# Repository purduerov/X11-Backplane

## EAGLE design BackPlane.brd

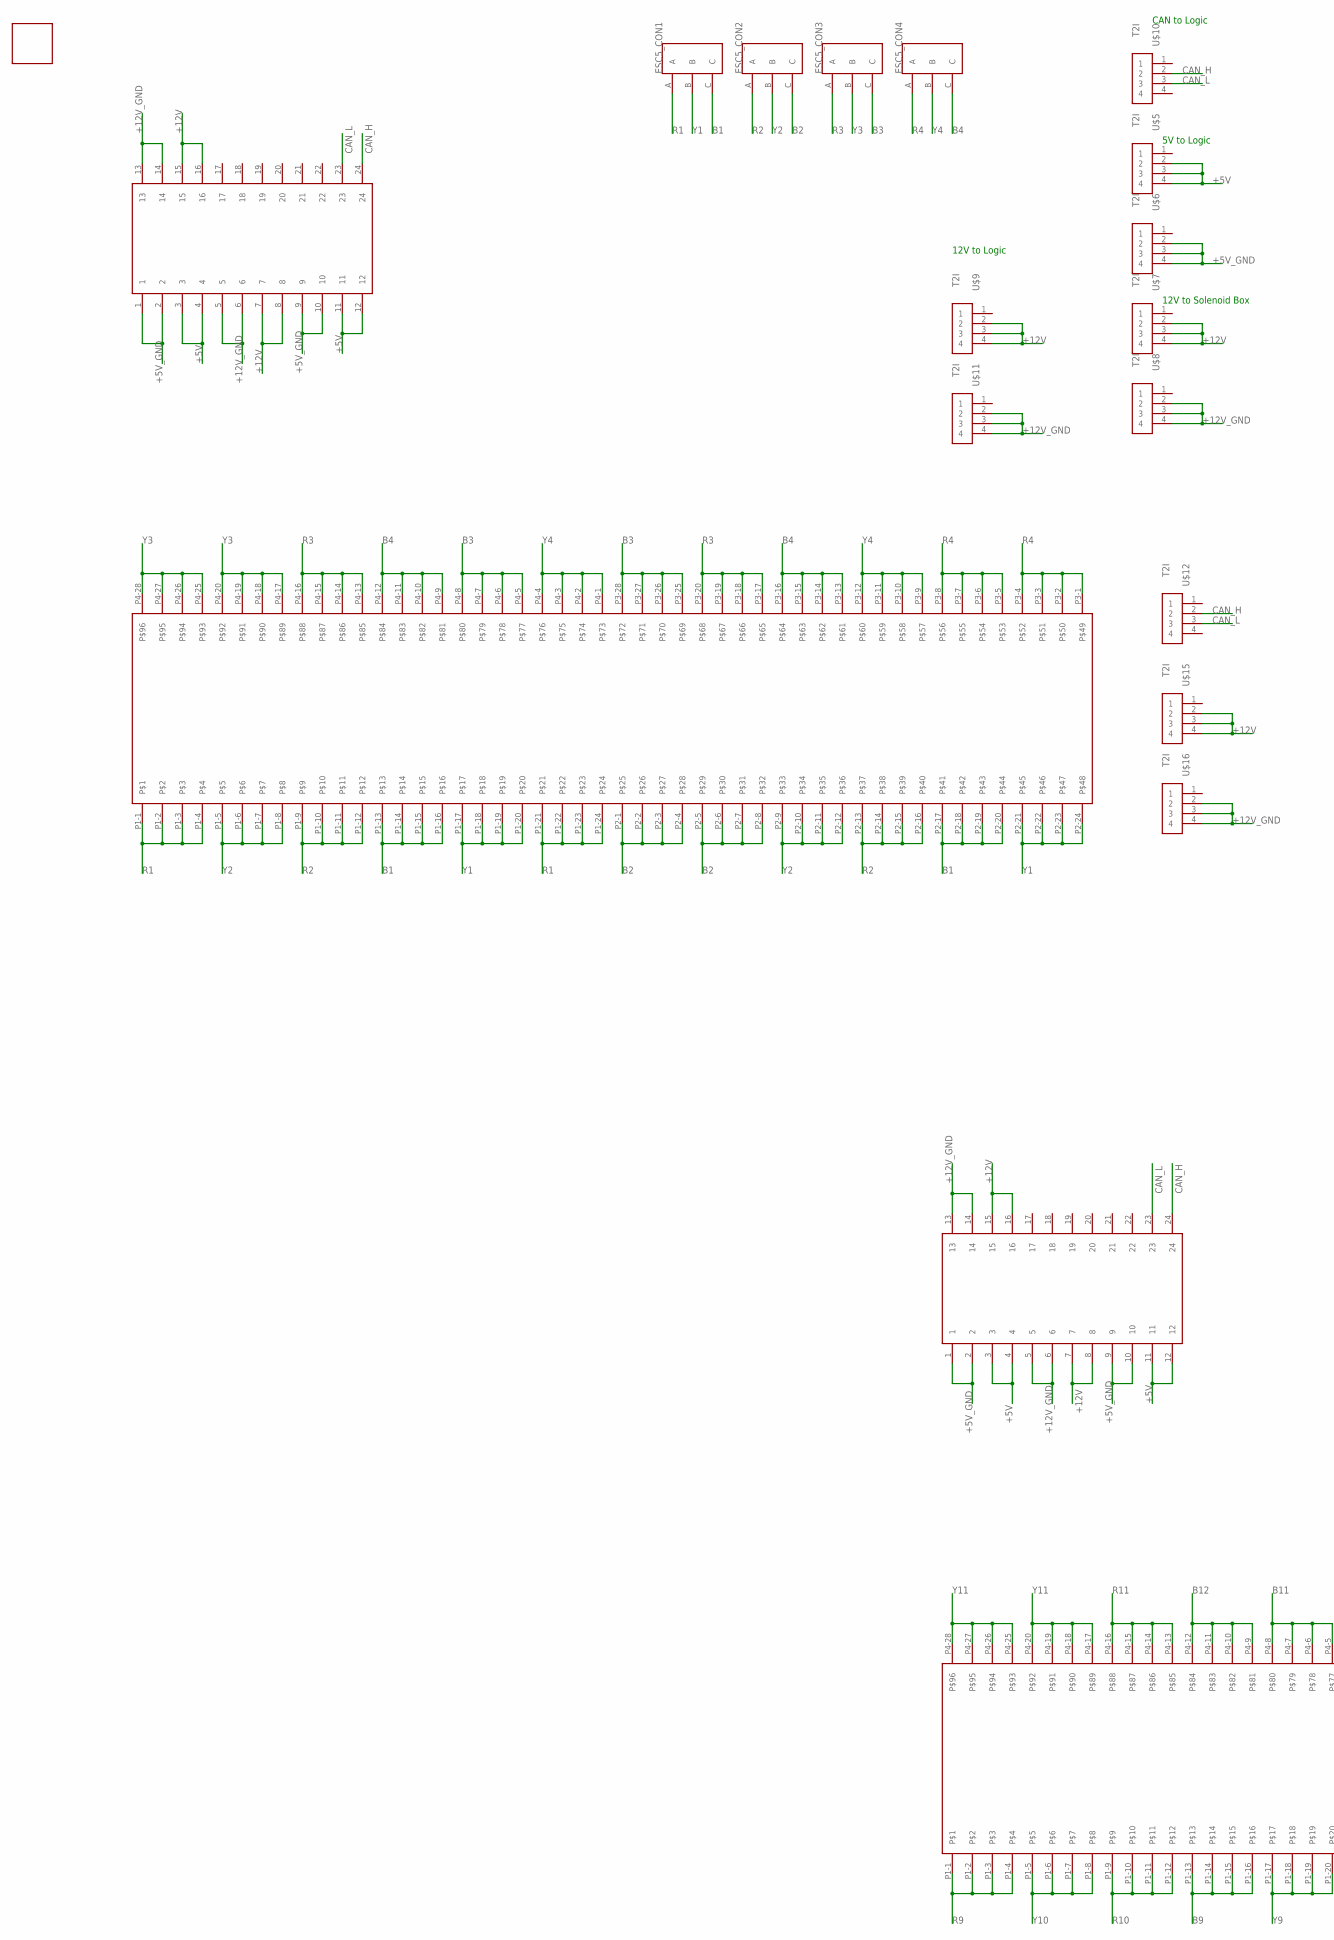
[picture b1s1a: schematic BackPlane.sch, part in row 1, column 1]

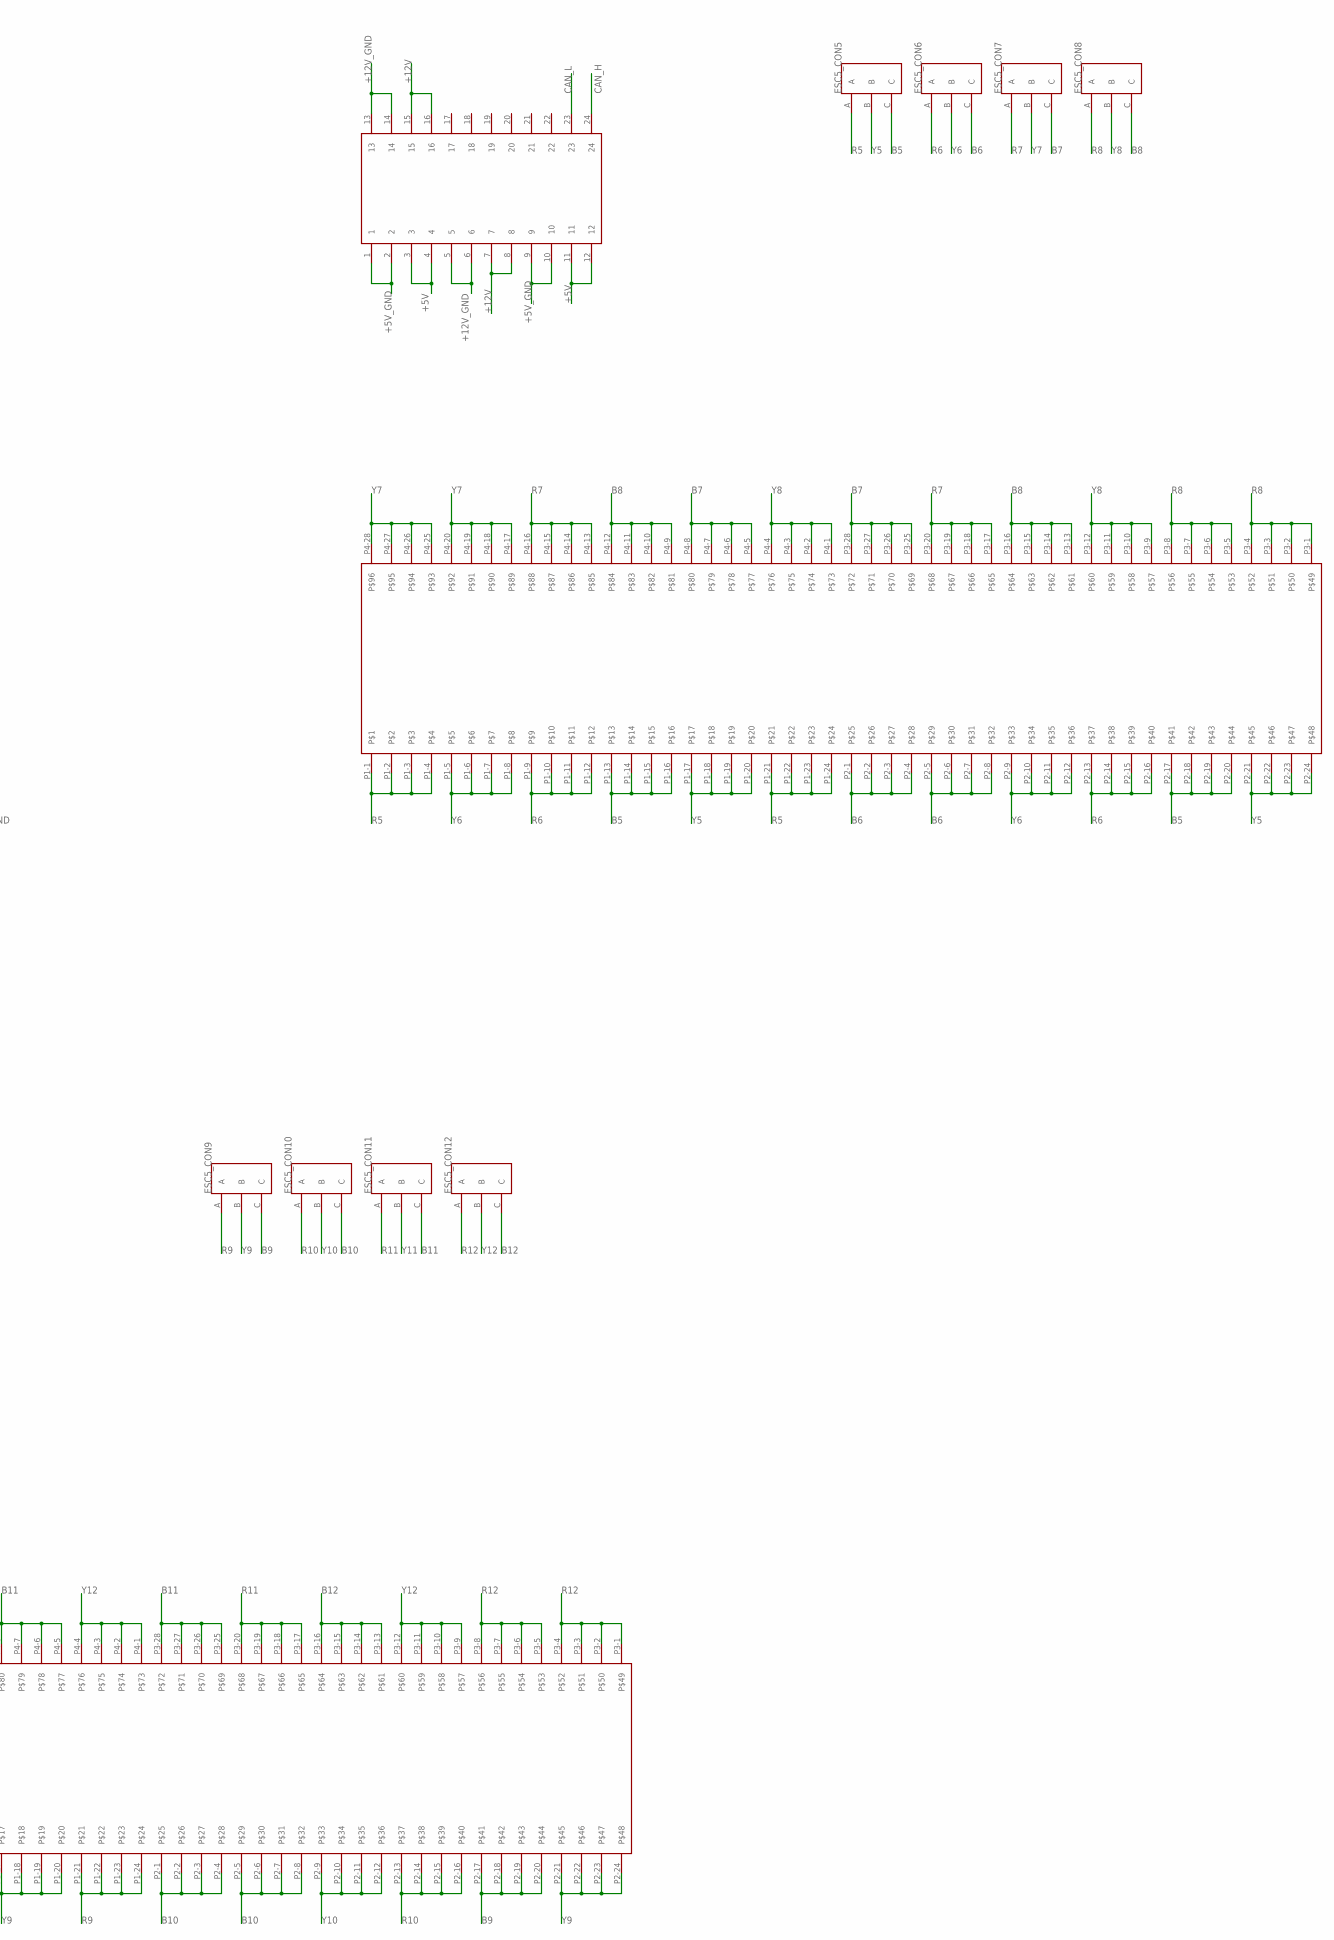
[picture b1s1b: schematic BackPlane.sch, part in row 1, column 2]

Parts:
ESC5_CON1, ESC5_CON2, ESC5_CON3, ESC5_CON4, ESC5_CON5, ESC5_CON6, ESC5_CON7, ESC5_CON8, ESC5_CON9, ESC5_CON10, ESC5_CON11, ESC5_CON12: 3PINCONNECTOR
U$1: BOARDBKP; BKP
U$2, U$3, U$4: THICC_CONNECTOR
U$5, U$6, U$7, U$8, U$9, U$10, U$11, U$12, U$15, U$16: T2I

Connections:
+5V: U$2.3, U$2.4, U$2.11, U$2.12, U$3.3, U$3.4, U$3.11, U$3.12, U$4.3, U$4.4, U$4.11, U$4.12, U$5.2, U$5.3, U$5.4
+5V_GND: U$2.1, U$2.2, U$2.9, U$2.10, U$3.1, U$3.2, U$3.9, U$3.10, U$4.1, U$4.2, U$4.9, U$4.10, U$6.2, U$6.3, U$6.4
+12V: U$2.7, U$2.8, U$2.15, U$2.16, U$3.7, U$3.8, U$3.15, U$3.16, U$4.7, U$4.8, U$4.15, U$4.16, U$7.2, U$7.3, U$7.4, U$9.2, U$9.3, U$9.4, U$15.2, U$15.3, U$15.4
+12V_GND: U$2.5, U$2.6, U$2.13, U$2.14, U$3.5, U$3.6, U$3.13, U$3.14, U$4.5, U$4.6, U$4.13, U$4.14, U$8.2, U$8.3, U$8.4, U$11.2, U$11.3, U$11.4, U$16.2, U$16.3, U$16.4
B1: ESC5_CON1.C, U$2.P1-13, U$2.P1-14, U$2.P1-15, U$2.P1-16, U$2.P2-17, U$2.P2-18, U$2.P2-19, U$2.P2-20
B2: ESC5_CON2.C, U$2.P2-1, U$2.P2-2, U$2.P2-3, U$2.P2-4, U$2.P2-5, U$2.P2-6, U$2.P2-7, U$2.P2-8
B3: ESC5_CON3.C, U$2.P3-25, U$2.P3-26, U$2.P3-27, U$2.P3-28, U$2.P4-5, U$2.P4-6, U$2.P4-7, U$2.P4-8
B4: ESC5_CON4.C, U$2.P3-13, U$2.P3-14, U$2.P3-15, U$2.P3-16, U$2.P4-9, U$2.P4-10, U$2.P4-11, U$2.P4-12
B5: ESC5_CON5.C, U$3.P1-13, U$3.P1-14, U$3.P1-15, U$3.P1-16, U$3.P2-17, U$3.P2-18, U$3.P2-19, U$3.P2-20
B6: ESC5_CON6.C, U$3.P2-1, U$3.P2-2, U$3.P2-3, U$3.P2-4, U$3.P2-5, U$3.P2-6, U$3.P2-7, U$3.P2-8
B7: ESC5_CON7.C, U$3.P3-25, U$3.P3-26, U$3.P3-27, U$3.P3-28, U$3.P4-5, U$3.P4-6, U$3.P4-7, U$3.P4-8
B8: ESC5_CON8.C, U$3.P3-13, U$3.P3-14, U$3.P3-15, U$3.P3-16, U$3.P4-9, U$3.P4-10, U$3.P4-11, U$3.P4-12
B9: ESC5_CON9.C, U$4.P1-13, U$4.P1-14, U$4.P1-15, U$4.P1-16, U$4.P2-17, U$4.P2-18, U$4.P2-19, U$4.P2-20
B10: ESC5_CON10.C, U$4.P2-1, U$4.P2-2, U$4.P2-3, U$4.P2-4, U$4.P2-5, U$4.P2-6, U$4.P2-7, U$4.P2-8
B11: ESC5_CON11.C, U$4.P3-25, U$4.P3-26, U$4.P3-27, U$4.P3-28, U$4.P4-5, U$4.P4-6, U$4.P4-7, U$4.P4-8
B12: ESC5_CON12.C, U$4.P3-13, U$4.P3-14, U$4.P3-15, U$4.P3-16, U$4.P4-9, U$4.P4-10, U$4.P4-11, U$4.P4-12
CAN_H: U$2.24, U$3.24, U$4.24, U$10.2, U$12.2
CAN_L: U$2.23, U$3.23, U$4.23, U$10.3, U$12.3
R1: ESC5_CON1.A, U$2.P1-1, U$2.P1-2, U$2.P1-3, U$2.P1-4, U$2.P1-21, U$2.P1-22, U$2.P1-23, U$2.P1-24
R2: ESC5_CON2.A, U$2.P1-9, U$2.P1-10, U$2.P1-11, U$2.P1-12, U$2.P2-13, U$2.P2-14, U$2.P2-15, U$2.P2-16
R3: ESC5_CON3.A, U$2.P3-17, U$2.P3-18, U$2.P3-19, U$2.P3-20, U$2.P4-13, U$2.P4-14, U$2.P4-15, U$2.P4-16
R4: ESC5_CON4.A, U$2.P3-1, U$2.P3-2, U$2.P3-3, U$2.P3-4, U$2.P3-5, U$2.P3-6, U$2.P3-7, U$2.P3-8
R5: ESC5_CON5.A, U$3.P1-1, U$3.P1-2, U$3.P1-3, U$3.P1-4, U$3.P1-21, U$3.P1-22, U$3.P1-23, U$3.P1-24
R6: ESC5_CON6.A, U$3.P1-9, U$3.P1-10, U$3.P1-11, U$3.P1-12, U$3.P2-13, U$3.P2-14, U$3.P2-15, U$3.P2-16
R7: ESC5_CON7.A, U$3.P3-17, U$3.P3-18, U$3.P3-19, U$3.P3-20, U$3.P4-13, U$3.P4-14, U$3.P4-15, U$3.P4-16
R8: ESC5_CON8.A, U$3.P3-1, U$3.P3-2, U$3.P3-3, U$3.P3-4, U$3.P3-5, U$3.P3-6, U$3.P3-7, U$3.P3-8
R9: ESC5_CON9.A, U$4.P1-1, U$4.P1-2, U$4.P1-3, U$4.P1-4, U$4.P1-21, U$4.P1-22, U$4.P1-23, U$4.P1-24
R10: ESC5_CON10.A, U$4.P1-9, U$4.P1-10, U$4.P1-11, U$4.P1-12, U$4.P2-13, U$4.P2-14, U$4.P2-15, U$4.P2-16
R11: ESC5_CON11.A, U$4.P3-17, U$4.P3-18, U$4.P3-19, U$4.P3-20, U$4.P4-13, U$4.P4-14, U$4.P4-15, U$4.P4-16
R12: ESC5_CON12.A, U$4.P3-1, U$4.P3-2, U$4.P3-3, U$4.P3-4, U$4.P3-5, U$4.P3-6, U$4.P3-7, U$4.P3-8
Y1: ESC5_CON1.B, U$2.P1-17, U$2.P1-18, U$2.P1-19, U$2.P1-20, U$2.P2-21, U$2.P2-22, U$2.P2-23, U$2.P2-24
Y2: ESC5_CON2.B, U$2.P1-5, U$2.P1-6, U$2.P1-7, U$2.P1-8, U$2.P2-9, U$2.P2-10, U$2.P2-11, U$2.P2-12
Y3: ESC5_CON3.B, U$2.P4-17, U$2.P4-18, U$2.P4-19, U$2.P4-20, U$2.P4-25, U$2.P4-26, U$2.P4-27, U$2.P4-28
Y4: ESC5_CON4.B, U$2.P3-9, U$2.P3-10, U$2.P3-11, U$2.P3-12, U$2.P4-1, U$2.P4-2, U$2.P4-3, U$2.P4-4
Y5: ESC5_CON5.B, U$3.P1-17, U$3.P1-18, U$3.P1-19, U$3.P1-20, U$3.P2-21, U$3.P2-22, U$3.P2-23, U$3.P2-24
Y6: ESC5_CON6.B, U$3.P1-5, U$3.P1-6, U$3.P1-7, U$3.P1-8, U$3.P2-9, U$3.P2-10, U$3.P2-11, U$3.P2-12
Y7: ESC5_CON7.B, U$3.P4-17, U$3.P4-18, U$3.P4-19, U$3.P4-20, U$3.P4-25, U$3.P4-26, U$3.P4-27, U$3.P4-28
Y8: ESC5_CON8.B, U$3.P3-9, U$3.P3-10, U$3.P3-11, U$3.P3-12, U$3.P4-1, U$3.P4-2, U$3.P4-3, U$3.P4-4
Y9: ESC5_CON9.B, U$4.P1-17, U$4.P1-18, U$4.P1-19, U$4.P1-20, U$4.P2-21, U$4.P2-22, U$4.P2-23, U$4.P2-24
Y10: ESC5_CON10.B, U$4.P1-5, U$4.P1-6, U$4.P1-7, U$4.P1-8, U$4.P2-9, U$4.P2-10, U$4.P2-11, U$4.P2-12
Y11: ESC5_CON11.B, U$4.P4-17, U$4.P4-18, U$4.P4-19, U$4.P4-20, U$4.P4-25, U$4.P4-26, U$4.P4-27, U$4.P4-28
Y12: ESC5_CON12.B, U$4.P3-9, U$4.P3-10, U$4.P3-11, U$4.P3-12, U$4.P4-1, U$4.P4-2, U$4.P4-3, U$4.P4-4

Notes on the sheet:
12V to Logic
12V to Solenoid Box
5V to Logic
CAN to Logic

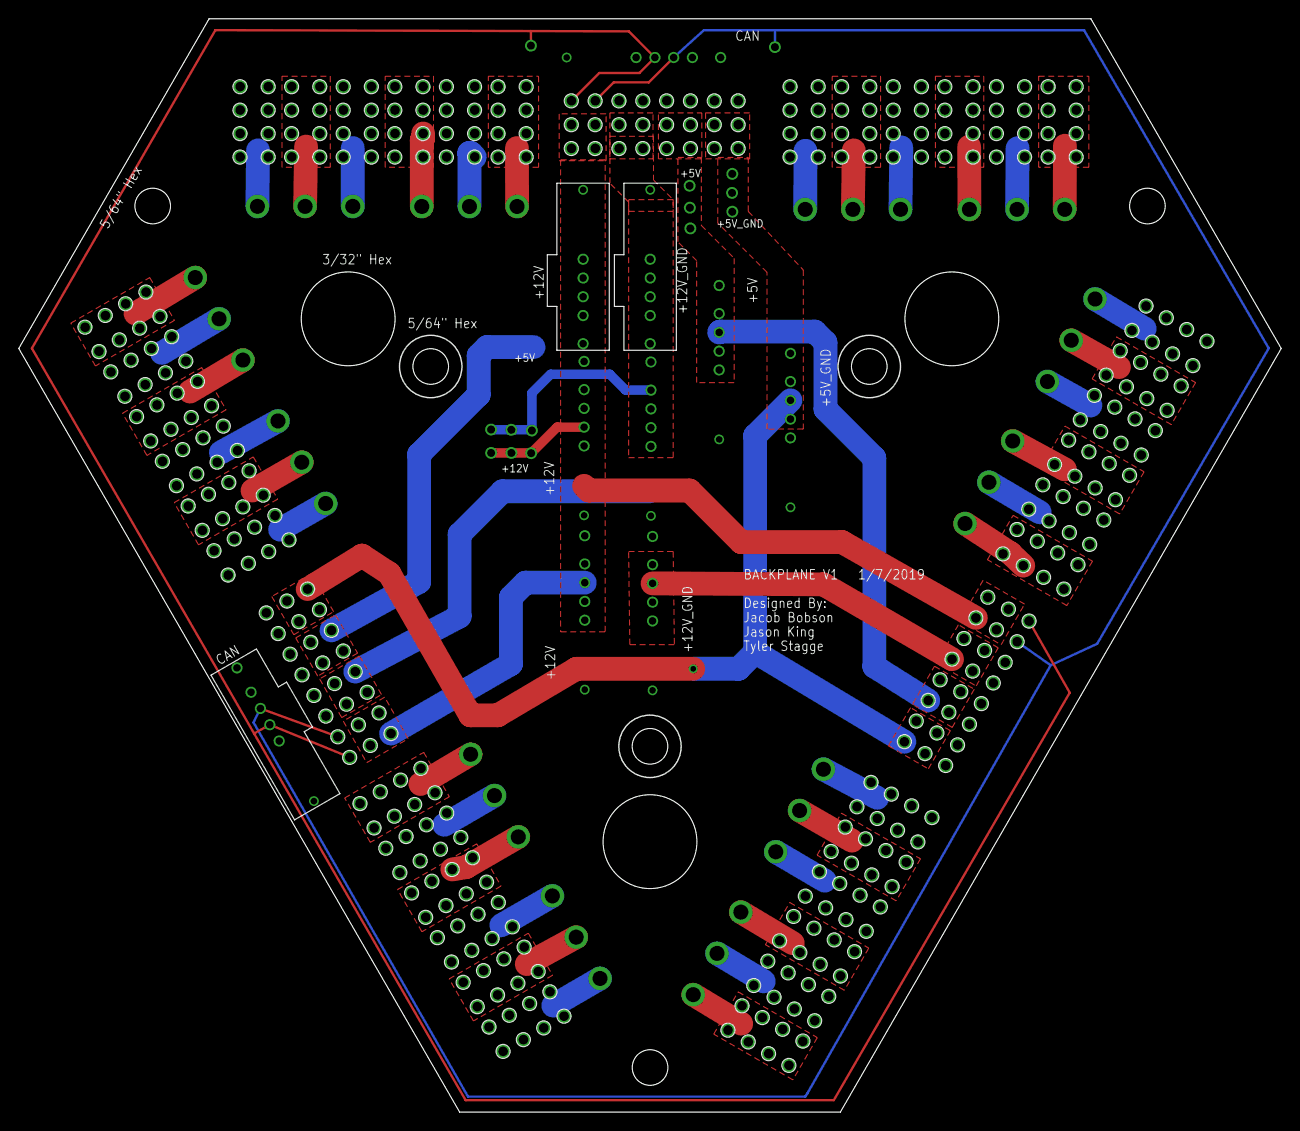
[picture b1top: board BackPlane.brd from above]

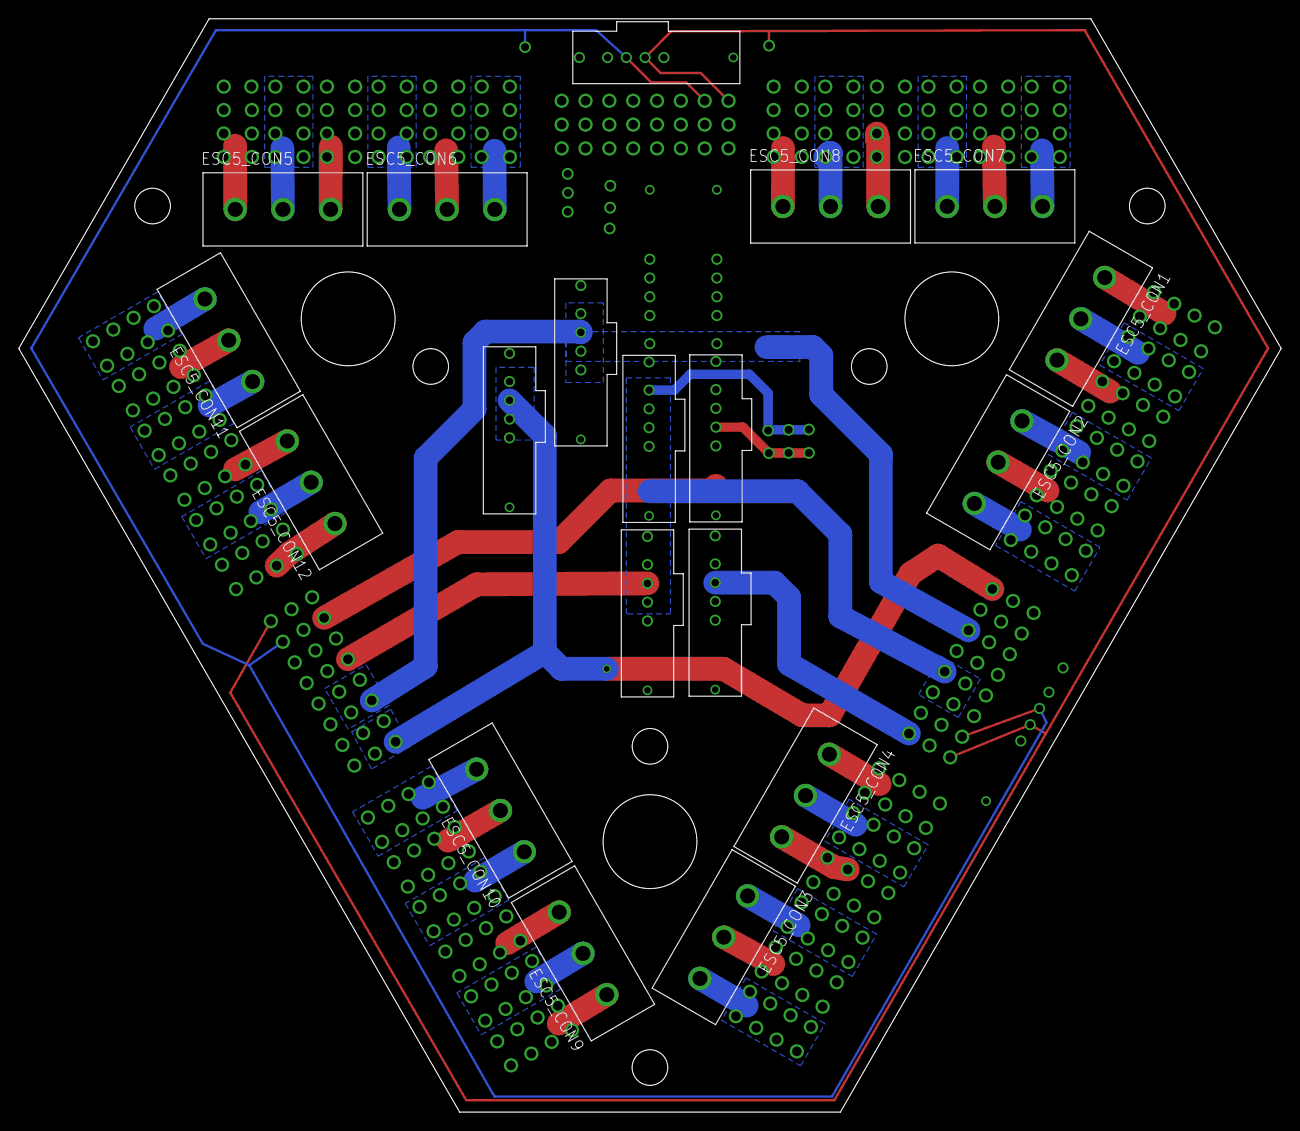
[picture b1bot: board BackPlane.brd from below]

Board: 2 copper layers, 134.6 x 116.5 mm, 26 parts (19 on the bottom side), 42 nets.

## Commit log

2018-09-19 Added gitignore
2018-10-25 Board Outline
2018-12-01 progress
2018-12-01 names
2018-12-01 Routing
2018-12-01 connectors
2018-12-03 More Routing
2019-01-07 Routed
2019-01-07 Fixed clearance issues between the polygons by making them alternate layers
2019-01-07 Things And Stuff
2019-01-11 final stuff
2019-01-12 Added image
